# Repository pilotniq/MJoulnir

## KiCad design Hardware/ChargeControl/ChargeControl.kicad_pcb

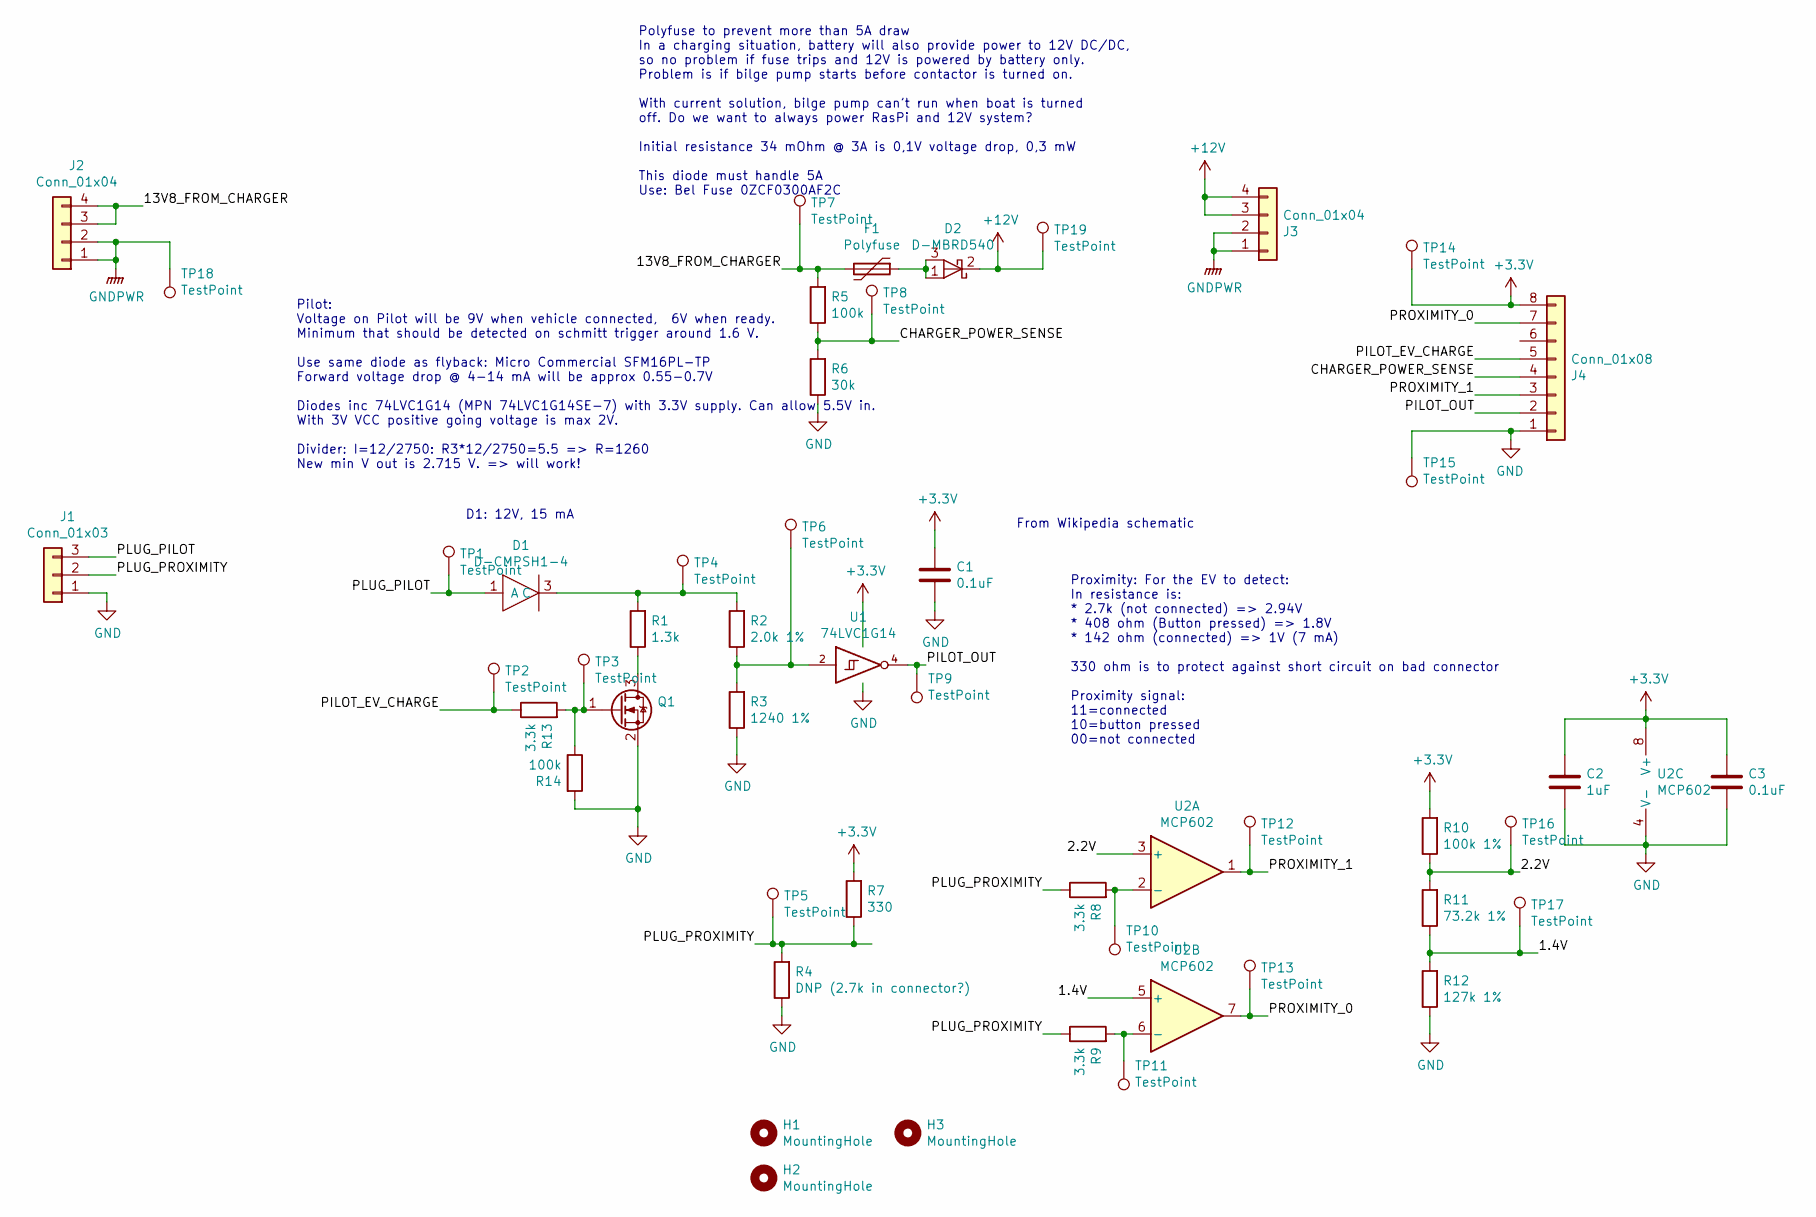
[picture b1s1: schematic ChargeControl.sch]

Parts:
C1, C3: 0.1uF; C_0603_1608Metric_Pad1.05x0.95mm_HandSolder
C2: 1uF; C_0603_1608Metric_Pad1.05x0.95mm_HandSolder
D1: D-CMPSH1-4; SOT23F
D2: D-MBRD540; TO-252-3_TabPin2
F1: Polyfuse; Fuse_2920_7451Metric_Pad2.10x5.45mm_HandSolder
H1, H2, H3: MountingHole; MountingHole_4.3mm_M4_ISO14580
J1: Conn_01x03; CON-MOLEX-CGRIDIII-1x3-RA-0901362203
J2, J3: Conn_01x04; CON-MOLEX-CGRIDIII-1x4-RA-0901362204
J4: Conn_01x08; CON-MOLEX-CGRIDIII-2x4-RA-0901303208
Q1: Q-FET-N-SSM3K36MFV; SOT-723
R1: 1.3k; R_0603_1608Metric_Pad1.05x0.95mm_HandSolder
R2: 2.0k 1%; R_0603_1608Metric_Pad1.05x0.95mm_HandSolder
R3: 1240 1%; R_0603_1608Metric_Pad1.05x0.95mm_HandSolder
R4: DNP (2.7k in connector?); R_0603_1608Metric_Pad1.05x0.95mm_HandSolder
R5, R14: 100k; R_0603_1608Metric_Pad1.05x0.95mm_HandSolder
R6: 30k; R_0603_1608Metric_Pad1.05x0.95mm_HandSolder
R7: 330; R_0603_1608Metric_Pad1.05x0.95mm_HandSolder
R8, R9, R13: 3.3k; R_0603_1608Metric_Pad1.05x0.95mm_HandSolder
R10: 100k 1%; R_0603_1608Metric_Pad1.05x0.95mm_HandSolder
R11: 73.2k 1%; R_0603_1608Metric_Pad1.05x0.95mm_HandSolder
R12: 127k 1%; R_0603_1608Metric_Pad1.05x0.95mm_HandSolder
TP1, TP2, TP3, TP4, TP5, TP6, TP7, TP8, TP9, TP10, TP11, TP12, TP13, TP14, TP15, TP16, TP17, TP18, TP19: TestPoint; TestPoint_Loop_D2.50mm_Drill1.0mm_LowProfile
U1: 74LVC1G14; SOT-353_SC-70-5_Handsoldering
U2: MCP602; SOIC-8_3.9x4.9mm_P1.27mm

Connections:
+3V3: C1.1, C2.1, C3.1, J4.8, R7.2, R10.2, TP14.1, U1.5 (VCC), U2.8 (V+)
+12V: D2.2 (K), J3.3, J3.4, TP19.1
/1.4V: R11.1, R12.2, TP17.1, U2.5 (+)
/2.2V: R10.1, R11.2, TP16.1, U2.3 (+)
/13V8_FROM_CHARGER: F1.2, J2.3, J2.4, R5.2, TP7.1
/CHARGER_POWER_SENSE: J4.4, R5.1, R6.2, TP8.1
/PILOT_EV_CHARGE: J4.5, R13.1, TP2.1
/PILOT_OUT: J4.2, TP9.1, U1.4
/PLUG_PILOT: D1.1 (A), J1.3, TP1.1
/PLUG_PROXIMITY: J1.2, R4.2, R7.1, R8.1, R9.1, TP5.1
/PROXIMITY_0: J4.7, TP13.1, U2.7
/PROXIMITY_1: J4.3, TP12.1, U2.1
GND: C1.2, C2.2, C3.2, J1.1, J4.1, Q1.2 (S), R3.1, R4.1, R6.1, R12.1, R14.2, TP15.1, U1.3 (GND), U2.4 (V-)
GNDPWR: J2.1, J2.2, J3.1, J3.2, TP18.1
unnamed: D1.3 (C), R1.2, R2.2, TP4.1
unnamed: D2.1 (A), D2.3, F1.1
unnamed: Q1.1 (G), R13.2, R14.1, TP3.1
unnamed: Q1.3 (D), R1.1
unnamed: R2.1, R3.2, TP6.1, U1.2
unnamed: R8.2, TP10.1, U2.2 (-)
unnamed: R9.2, TP11.1, U2.6 (-)

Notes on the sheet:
Polyfuse to prevent more than 5A draw In a charging situation, battery will also provide power to 12V DC/DC, so no problem if fuse trips and 12V is powered by battery only. Problem is if bilge pump starts before contactor is turned on. With current solution, bilge pump can’t run when boat is turned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
From Wikipedia schematic
D1: 12V, 15 mA
Proximity: For the EV to detect: In resistance is: * 2.7k (not connected) => 2.94V * 408 ohm (Button pressed) => 1.8V * 142 ohm (connected) => 1V (7 mA) 330 ohm is to protect against short circuit on bad connector Proximity signal: 11=connected 10=button pressed 00=not connected
Pilot: Voltage on Pilot will be 9V when vehicle connected, 6V when ready. Minimum that should be detected on schmitt trigger around 1.6 V. Use same diode as flyback: Micro Commercial SFM16PL-TP Forward voltage drop @ 4-14 mA will be approx 0.55-0.7V Diodes inc 74LVC1G14 (MPN 74LVC1G14SE-7) with 3.3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

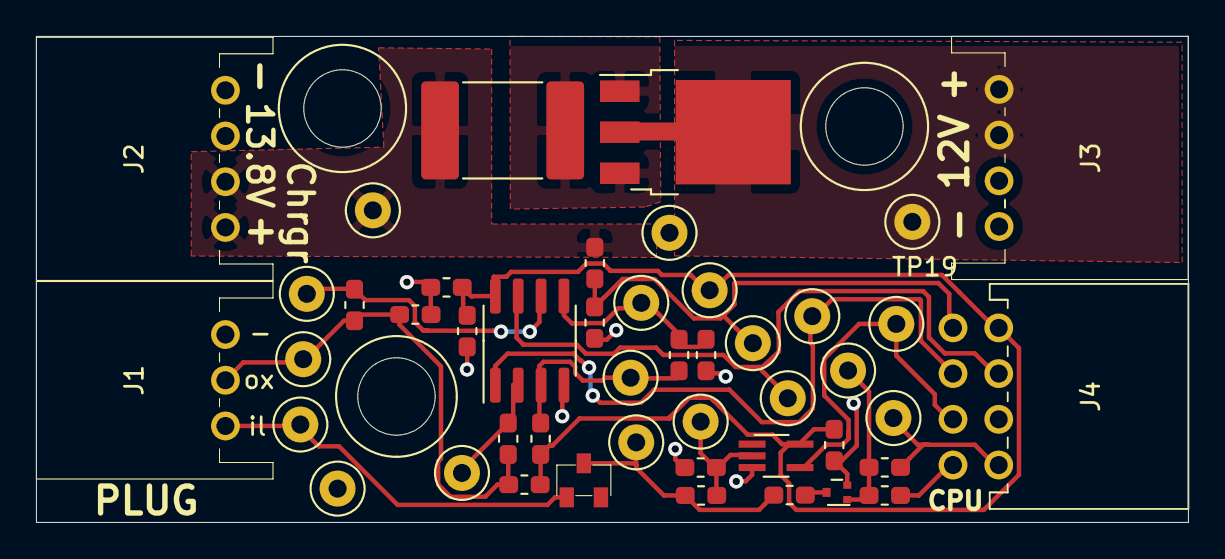
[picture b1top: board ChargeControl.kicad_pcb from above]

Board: 2 copper layers, 64.0 x 27.0 mm, 49 parts (0 on the bottom side), 21 nets.

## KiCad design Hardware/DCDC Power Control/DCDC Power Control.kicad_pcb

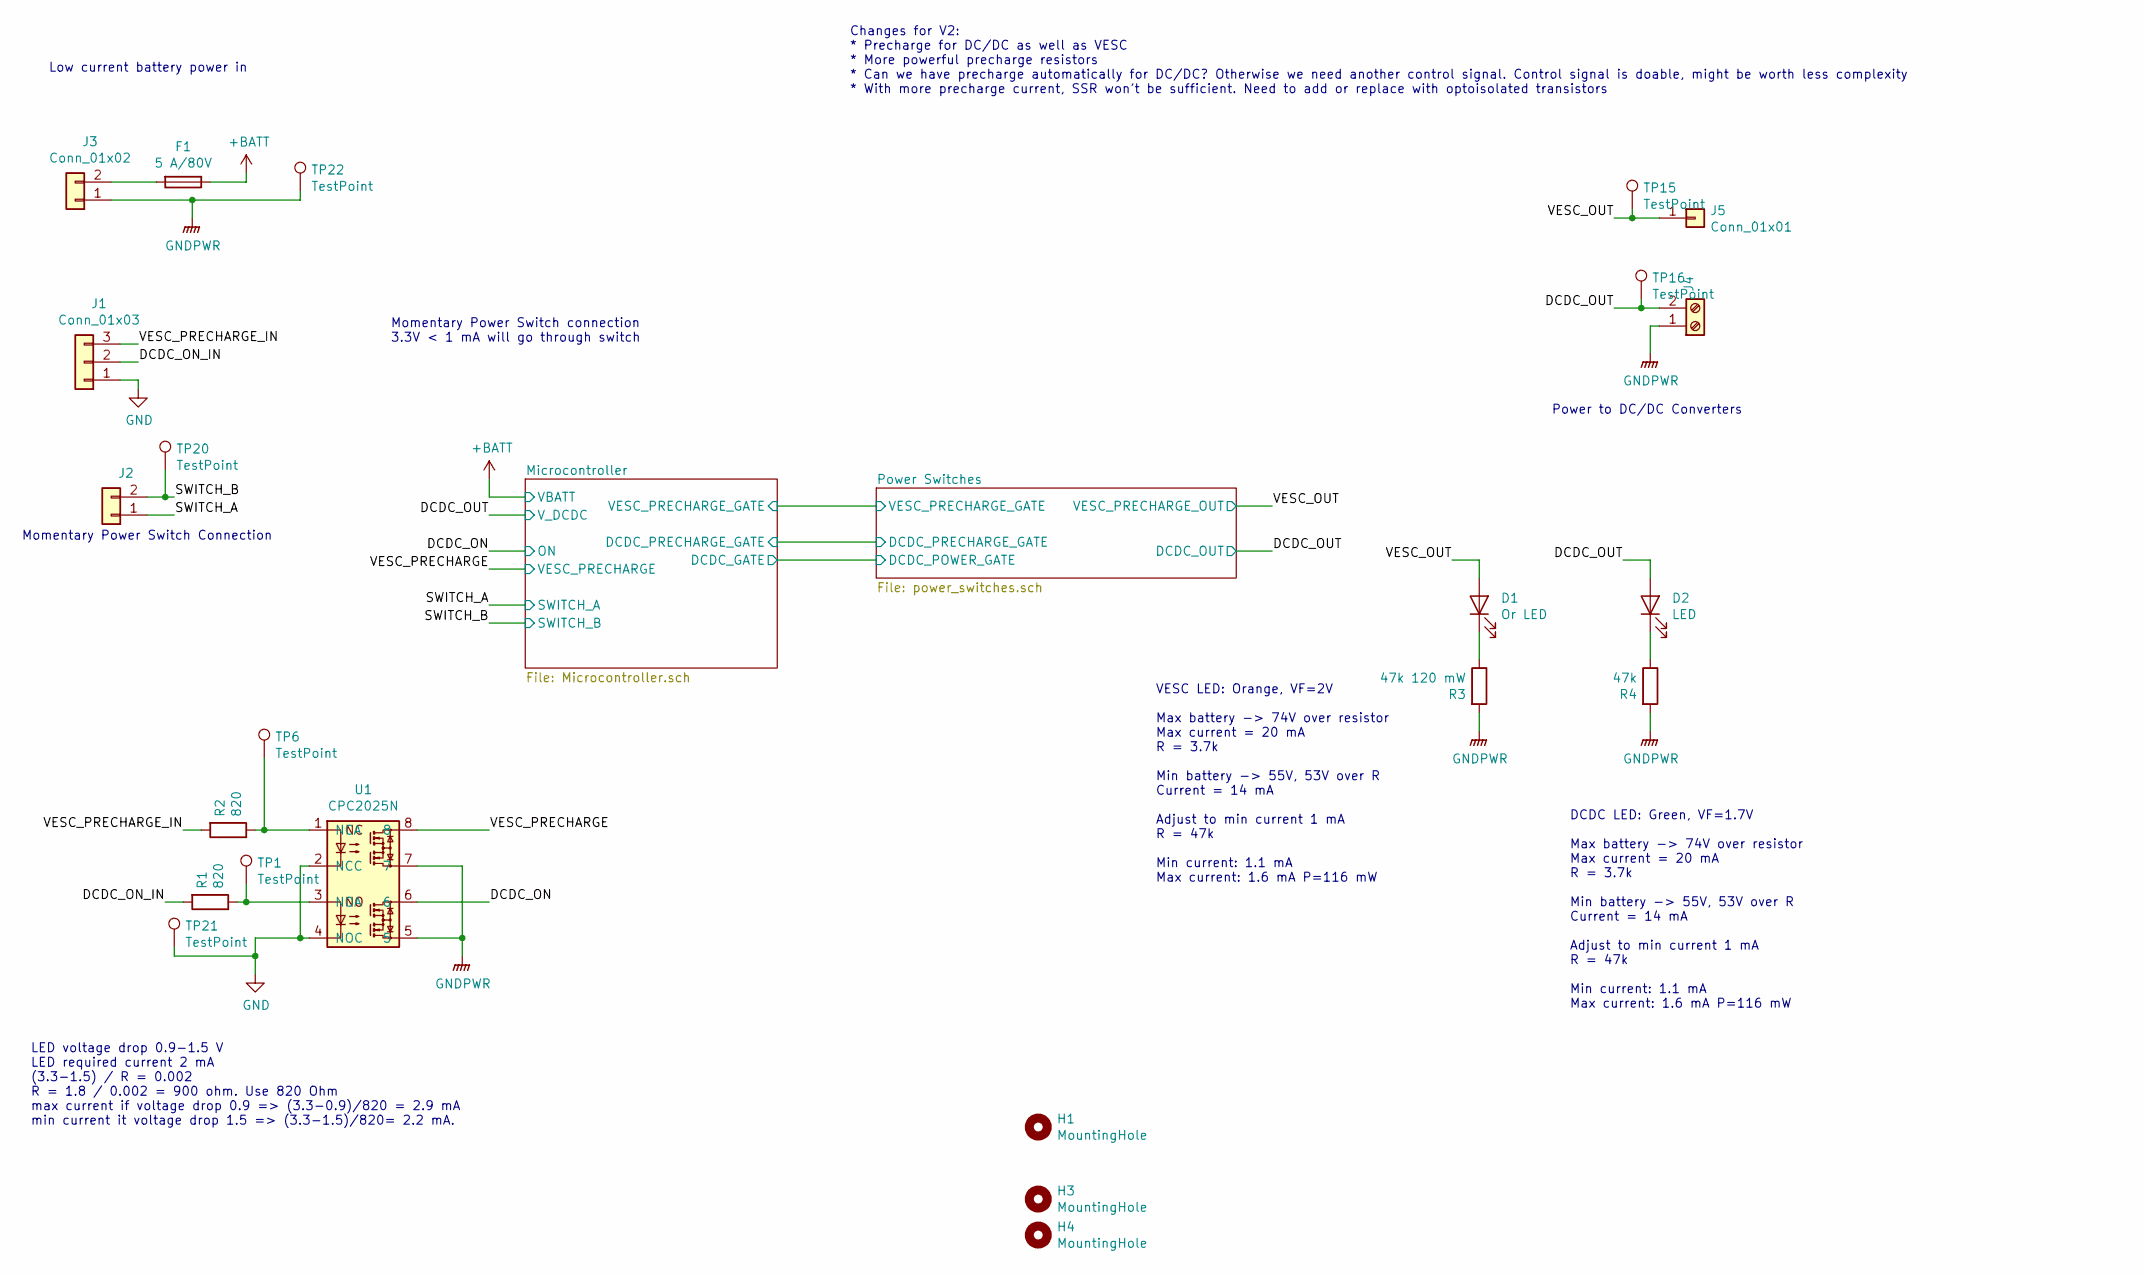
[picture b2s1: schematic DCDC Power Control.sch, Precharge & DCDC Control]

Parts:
D1: Or LED; LED_0603_1608Metric_Pad1.05x0.95mm_HandSolder
D2: LED; LED_0603_1608Metric_Pad1.05x0.95mm_HandSolder
F1: 5 A/80V; FUSE-KEYSTONE-3557-2
H1, H3, H4: MountingHole; MountingHole_4.3mm_M4_ISO14580
J1: Conn_01x03; CON-MOLEX-CGRIDIII-1x3-RA-0901362203
J2: Conn_01x02; CON-MOLEX-CGRIDIII-1x2 RA-0901362202
J3: Conn_01x02; AMASS_XT30PW-M_1x02_P2.50mm_Horizontal
J4: Screw_Terminal_01x02; AMASS_XT30PW-F_1x02_P2.50mm_Horizontal
J5: Conn_01x01; CON-SCREW-KEYSTONE-VERTICAL
R1, R2: 820; R_0603_1608Metric_Pad1.05x0.95mm_HandSolder
R3: 47k 120 mW; R_0603_1608Metric_Pad1.05x0.95mm_HandSolder
R4: 47k; R_0603_1608Metric_Pad1.05x0.95mm_HandSolder
TP1, TP6, TP15, TP16, TP20, TP21, TP22: TestPoint; TestPoint_Loop_D2.50mm_Drill1.0mm_LowProfile
U1: CPC2025N; SOIC-8_9.3x3.8mm_P2.54mm

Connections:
+BATT: F1.1; also elsewhere on the board
/DCDC_ON: U1.6; also elsewhere on the board
/DCDC_ON_IN: J1.2, R1.2
/DCDC_OUT: D2.2 (A), J4.2, TP16.1; also elsewhere on the board
/SWITCH_B: J2.2, TP20.1; also elsewhere on the board
/VESC_OUT: D1.2 (A), J5.1, TP15.1; also elsewhere on the board
/VESC_PRECHARGE: U1.8; also elsewhere on the board
/VESC_PRECHARGE_IN: J1.3, R2.2
GND: J1.1, TP21.1, U1.2 (NCC), U1.4 (NOC)
GNDPWR: J2.1, J3.1, J4.1, R3.2, R4.2, TP22.1, U1.5, U1.7; also elsewhere on the board
unnamed: D1.1 (K), R3.1
unnamed: D2.1 (K), R4.1
unnamed: F1.2, J3.2
unnamed: R1.1, TP1.1, U1.3 (NOA)
unnamed: R2.1, TP6.1, U1.1 (NCA)

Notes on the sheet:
Low current battery power in
Momentary Power Switch Connection
Power to DC/DC Converters
Momentary Power Switch connection 3.3V < 1 mA will go through switch
LED voltage drop 0.9-1.5 V LED required current 2 mA (3.3-1.5) / R = 0.002 R = 1.8 / 0.002 = 900 ohm. Use 820 Ohm max current if voltage drop 0.9 => (3.3-0.9)/820 = 2.9 mA min current it voltage drop 1.5 => (3.3-1.5)/820= 2.2 mA.
Changes for V2: * Precharge for DC/DC as well as VESC * More powerful precharge resistors * Can we have precharge automatically for DC/DC? Otherwise we need another control signal. Control signal is doable, might be worth less complexity * With more precharge current, SSR won’t be sufficient. Need 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
VESC LED: Orange, VF=2V Max battery -> 74V over resistor Max current = 20 mA R = 3.7k Min battery -> 55V, 53V over R Current = 14 mA Adjust to min current 1 mA R = 47k Min current: 1.1 mA Max current: 1.6 mA P=116 mW
DCDC LED: Green, VF=1.7V Max battery -> 74V over resistor Max current = 20 mA R = 3.7k Min battery -> 55V, 53V over R Current = 14 mA Adjust to min current 1 mA R = 47k Min current: 1.1 mA Max current: 1.6 mA P=116 mW

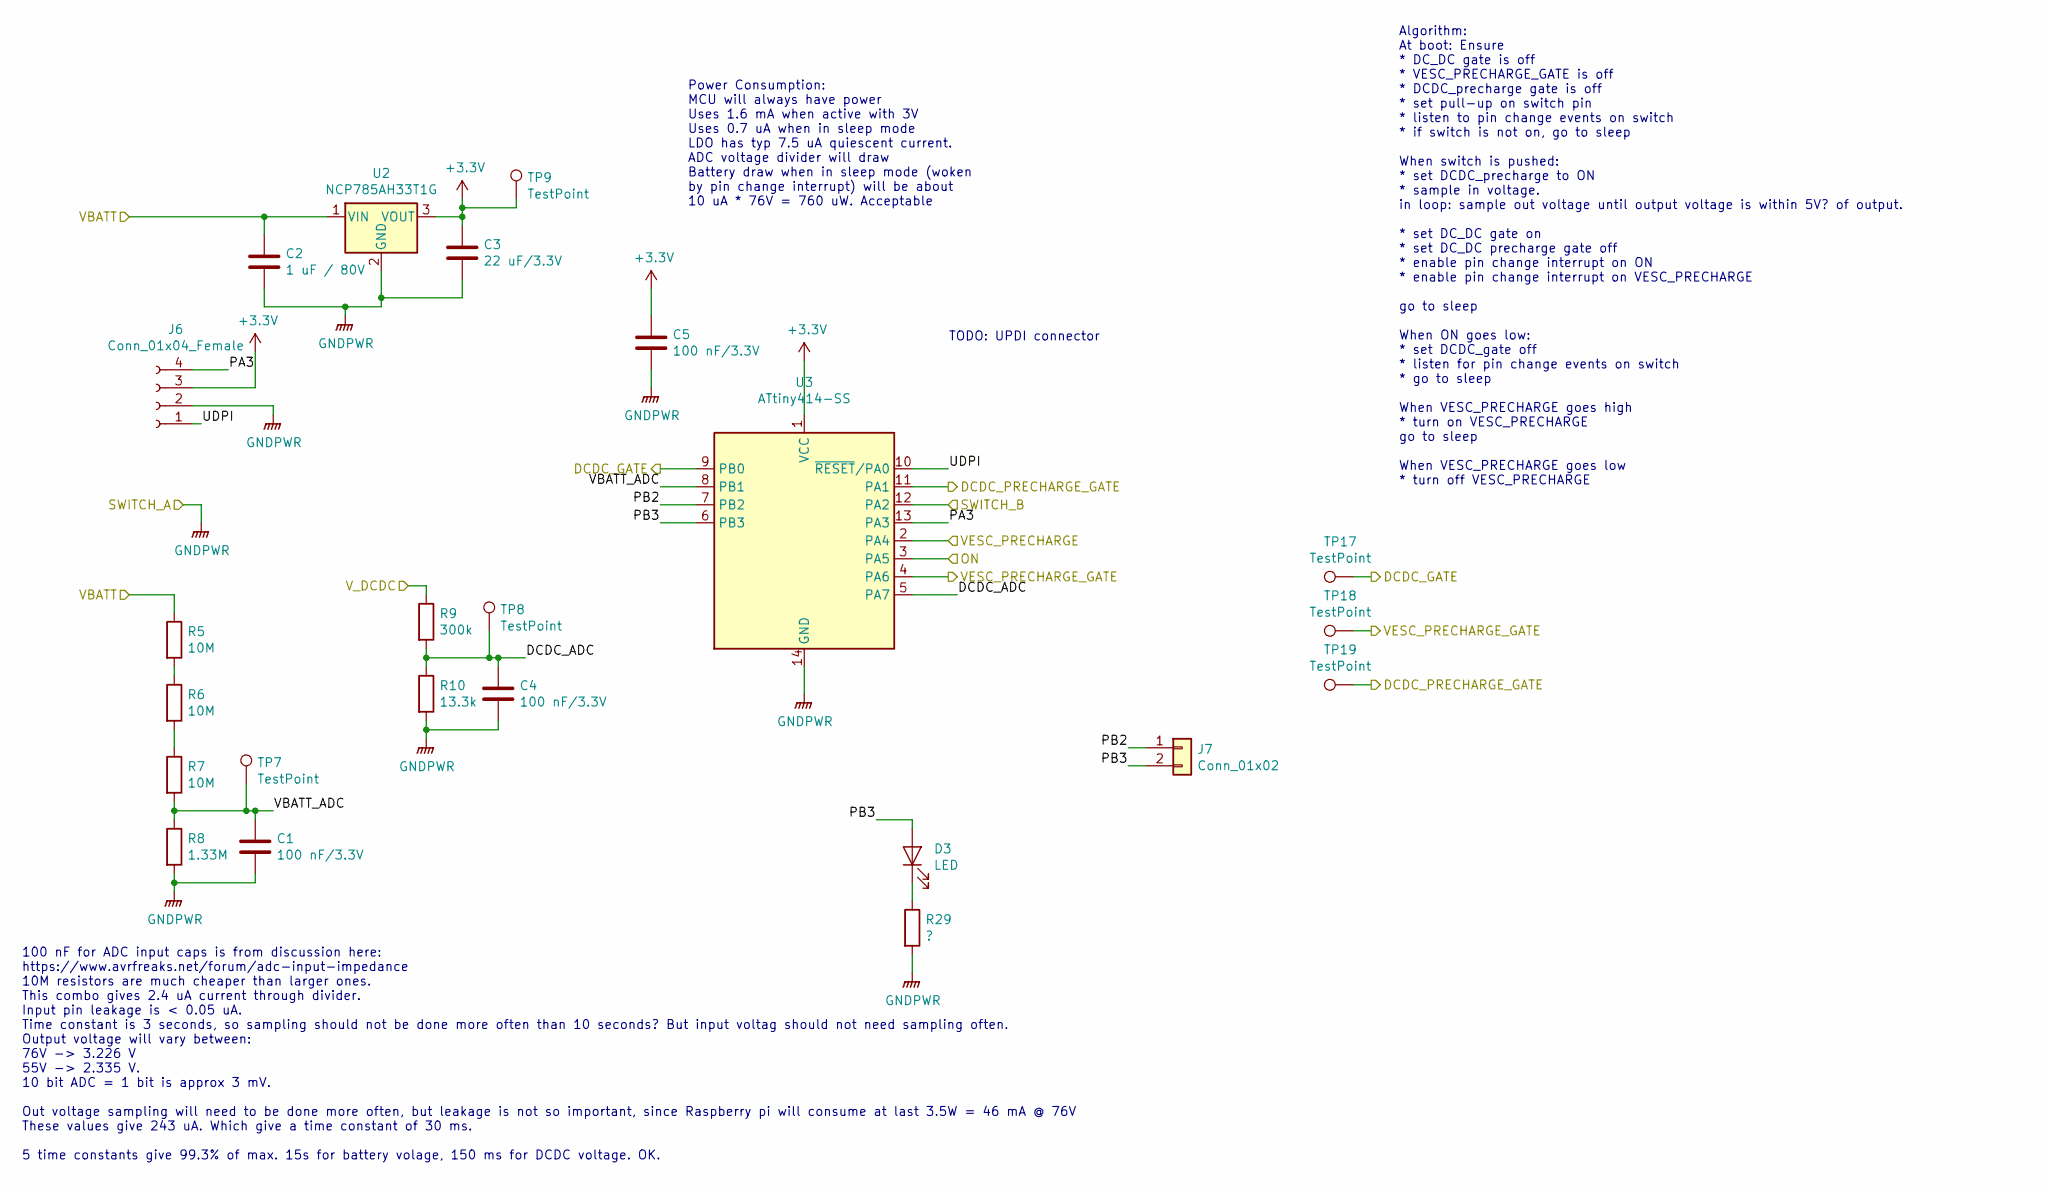
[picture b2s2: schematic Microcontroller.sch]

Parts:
C1, C4, C5: 100 nF/3.3V; C_0603_1608Metric_Pad1.05x0.95mm_HandSolder
C2: 1 uF / 80V; C_1206_3216Metric_Pad1.42x1.75mm_HandSolder
C3: 22 uF/3.3V; C_0805_2012Metric_Pad1.15x1.40mm_HandSolder
D3: LED; LED_0603_1608Metric_Castellated
J6: Conn_01x04_Female; PinSocket_1x04_P2.54mm_Vertical
J7: Conn_01x02; PinHeader_1x02_P2.54mm_Vertical
R5, R6, R7: 10M; R_0603_1608Metric_Pad1.05x0.95mm_HandSolder
R8: 1.33M; R_0603_1608Metric_Pad1.05x0.95mm_HandSolder
R9: 300k; R_0603_1608Metric_Pad1.05x0.95mm_HandSolder
R10: 13.3k; R_0603_1608Metric_Pad1.05x0.95mm_HandSolder
R29: ?; R_0603_1608Metric_Pad1.05x0.95mm_HandSolder
TP7, TP8, TP9, TP17, TP18, TP19: TestPoint; TestPoint_Loop_D2.50mm_Drill1.0mm_LowProfile
U2: NCP785AH33T1G; SOT-89-3
U3: ATtiny414-SS; SOIC-14_3.9x8.7mm_P1.27mm

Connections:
+3V3: C3.1, C5.1, J6.3, TP9.1, U2.3 (VOUT), U3.1 (VCC)
+BATT: C2.1, R5.1, U2.1 (VIN); also elsewhere on the board
/DCDC_ON: U3.3 (PA5); also elsewhere on the board
/DCDC_OUT: R9.1; also elsewhere on the board
/Microcontroller/DCDC_ADC: C4.1, R9.2, R10.1, TP8.1, U3.5 (PA7)
/Microcontroller/DCDC_GATE: TP17.1, U3.9 (PB0); also elsewhere on the board
/Microcontroller/DCDC_PRECHARGE_GATE: TP19.1, U3.11 (PA1); also elsewhere on the board
/Microcontroller/PA3: J6.4, U3.13 (PA3)
/Microcontroller/PB2: J7.1, U3.7 (PB2)
/Microcontroller/PB3: D3.2 (A), J7.2, U3.6 (PB3)
/Microcontroller/UDPI: J6.1, U3.10 (~RESET~/PA0)
/Microcontroller/VBATT_ADC: C1.1, R7.2, R8.1, TP7.1, U3.8 (PB1)
/Microcontroller/VESC_PRECHARGE_GATE: TP18.1, U3.4 (PA6); also elsewhere on the board
/SWITCH_B: U3.12 (PA2); also elsewhere on the board
/VESC_PRECHARGE: U3.2 (PA4); also elsewhere on the board
GNDPWR: C1.2, C2.2, C3.2, C4.2, C5.2, J6.2, R8.2, R10.2, R29.2, U2.2 (GND), U3.14 (GND); also elsewhere on the board
unnamed: D3.1 (K), R29.1
unnamed: R5.2, R6.1
unnamed: R6.2, R7.1

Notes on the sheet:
Power Consumption: MCU will always have power Uses 1.6 mA when active with 3V Uses 0.7 uA when in sleep mode LDO has typ 7.5 uA quiescent current. ADC voltage divider will draw Battery draw when in sleep mode (woken by pin change interrupt) will be about 10 uA * 76V = 760 uW. Acceptable
100 nF for ADC input caps is from discussion here: https://www.avrfreaks.net/forum/adc-input-impedance 10M resistors are much cheaper than larger ones. This combo gives 2.4 uA current through divider. Input pin leakage is < 0.05 uA. Time constant is 3 seconds, so sampling should not be done more of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
Algorithm: At boot: Ensure * DC_DC gate is off * VESC_PRECHARGE_GATE is off * DCDC_precharge gate is off * set pull-up on switch pin * listen to pin change events on switch * if switch is not on, go to sleep When switch is pushed: * set DCDC_precharge to ON * sample in voltage. in loop: sample out 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
TODO: UPDI connector

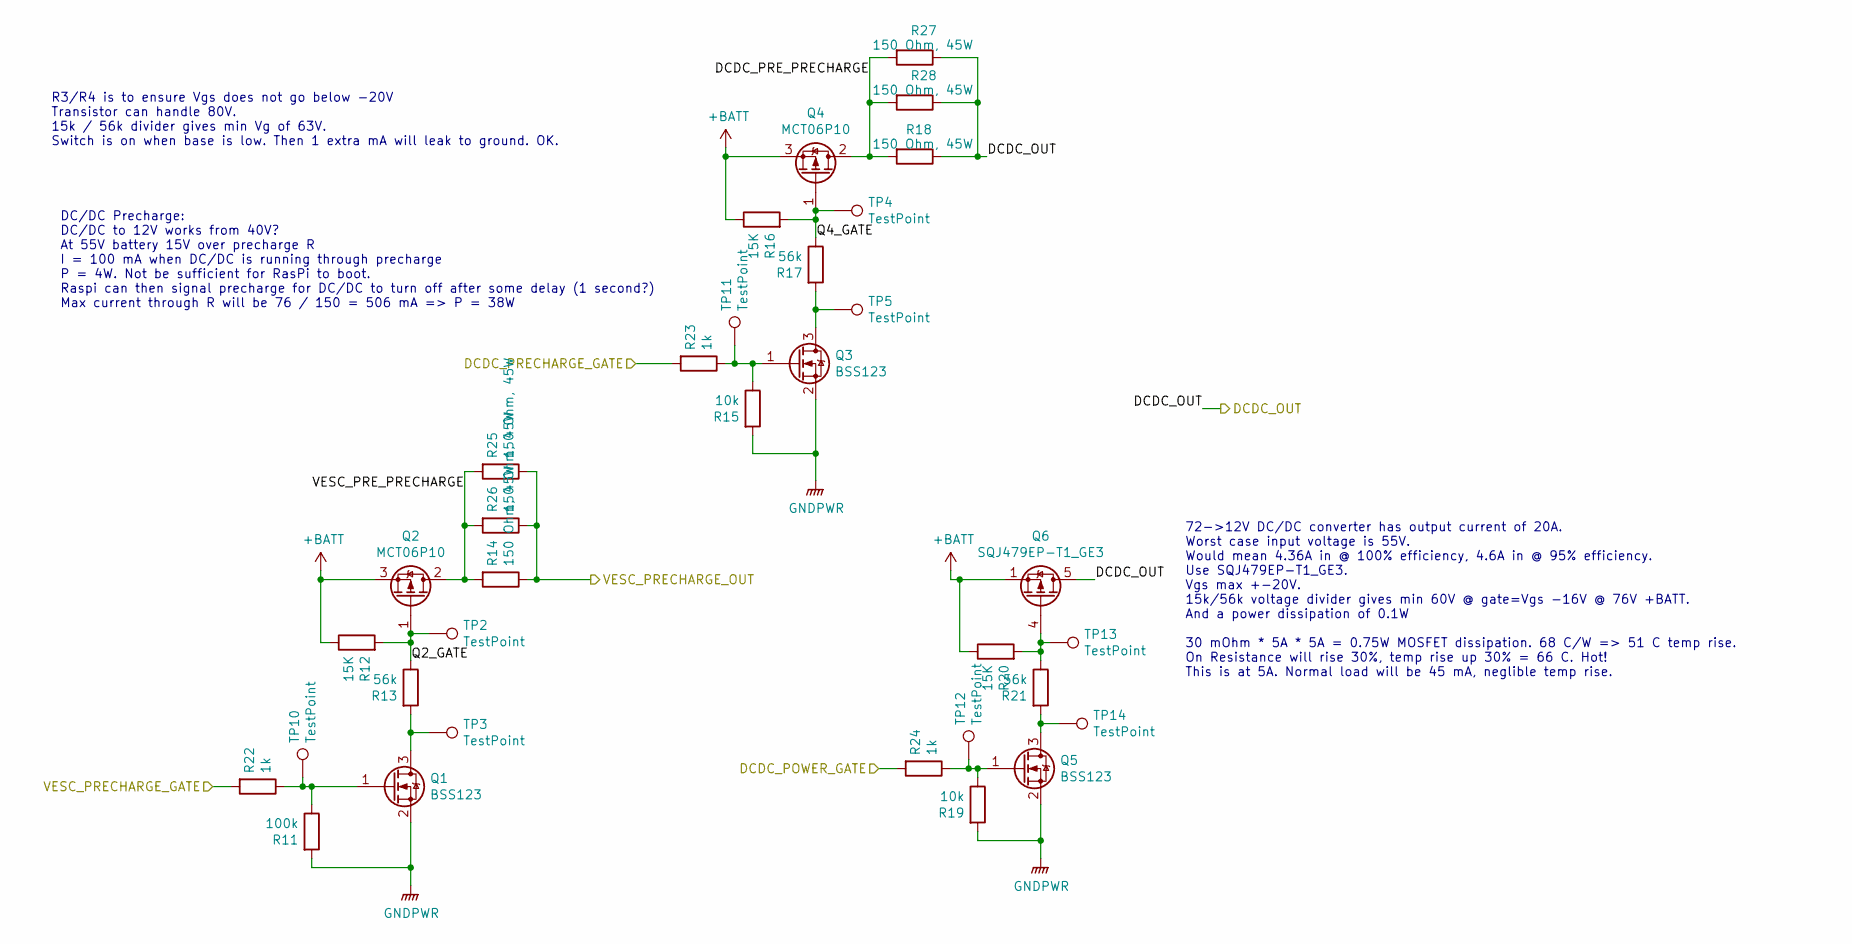
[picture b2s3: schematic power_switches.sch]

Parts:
Q1, Q3, Q5: BSS123; SOT-23
Q2, Q4: MCT06P10; SOT-223-3_TabPin2
Q6: SQJ479EP-T1_GE3; Q-VISHAY-PowerPAK SO-8L Single
R11: 100k; R_0603_1608Metric_Pad1.05x0.95mm_HandSolder
R12, R16, R20: 15K; R_0603_1608Metric_Pad1.05x0.95mm_HandSolder
R13, R17, R21: 56k; R_0603_1608Metric_Pad1.05x0.95mm_HandSolder
R14, R18, R25, R26, R27, R28: 150 Ohm, 45W; R_Radial_Power_L13.0mm_W9.0mm_P5.00mm
R15, R19: 10k; R_0603_1608Metric_Pad1.05x0.95mm_HandSolder
R22, R23, R24: 1k; R_0603_1608Metric_Pad1.05x0.95mm_HandSolder
TP2, TP3, TP4, TP5, TP10, TP11, TP12, TP13, TP14: TestPoint; TestPoint_Loop_D2.50mm_Drill1.0mm_LowProfile

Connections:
+BATT: Q2.3 (S), Q4.3 (S), Q6.1 (S), Q6.2 (S), Q6.3 (S), R12.1, R16.1, R20.1; also elsewhere on the board
/DCDC_OUT: Q6.5 (D), R18.1, R27.1, R28.1; also elsewhere on the board
/Microcontroller/DCDC_GATE: R24.2; also elsewhere on the board
/Microcontroller/DCDC_PRECHARGE_GATE: R23.2; also elsewhere on the board
/Microcontroller/VESC_PRECHARGE_GATE: R22.2; also elsewhere on the board
/Power Switches/DCDC_PRE_PRECHARGE: Q4.2 (D), R18.2, R27.2, R28.2
/Power Switches/Q2_GATE: Q2.1 (G), R12.2, R13.1, TP2.1
/Power Switches/Q4_GATE: Q4.1 (G), R16.2, R17.1, TP4.1
/Power Switches/VESC_PRE_PRECHARGE: Q2.2 (D), R14.2, R25.2, R26.2
/VESC_OUT: R14.1, R25.1, R26.1; also elsewhere on the board
GNDPWR: Q1.2 (S), Q3.2 (S), Q5.2 (S), R11.2, R15.2, R19.2; also elsewhere on the board
unnamed: Q1.1 (G), R11.1, R22.1, TP10.1
unnamed: Q1.3 (D), R13.2, TP3.1
unnamed: Q3.1 (G), R15.1, R23.1, TP11.1
unnamed: Q3.3 (D), R17.2, TP5.1
unnamed: Q5.1 (G), R19.1, R24.1, TP12.1
unnamed: Q5.3 (D), R21.2, TP14.1
unnamed: Q6.4 (G), R20.2, R21.1, TP13.1

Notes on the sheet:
R3/R4 is to ensure Vgs does not go below -20V Transistor can handle 80V. 15k / 56k divider gives min Vg of 63V. Switch is on when base is low. Then 1 extra mA will leak to ground. OK.
72->12V DC/DC converter has output current of 20A. Worst case input voltage is 55V. Would mean 4.36A in @ 100% efficiency, 4.6A in @ 95% efficiency. Use SQJ479EP-T1_GE3. Vgs max +-20V. 15k/56k voltage divider gives min 60V @ gate=Vgs -16V @ 76V +BATT. And a power dissipation of 0.1W 30 mOhm * 5A * 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
DC/DC Precharge: DC/DC to 12V works from 40V? At 55V battery 15V over precharge R I = 100 mA when DC/DC is running through precharge P = 4W. Not be sufficient for RasPi to boot. Raspi can then signal precharge for DC/DC to turn off after some delay (1 second?) Max current through R will be 76 / 150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

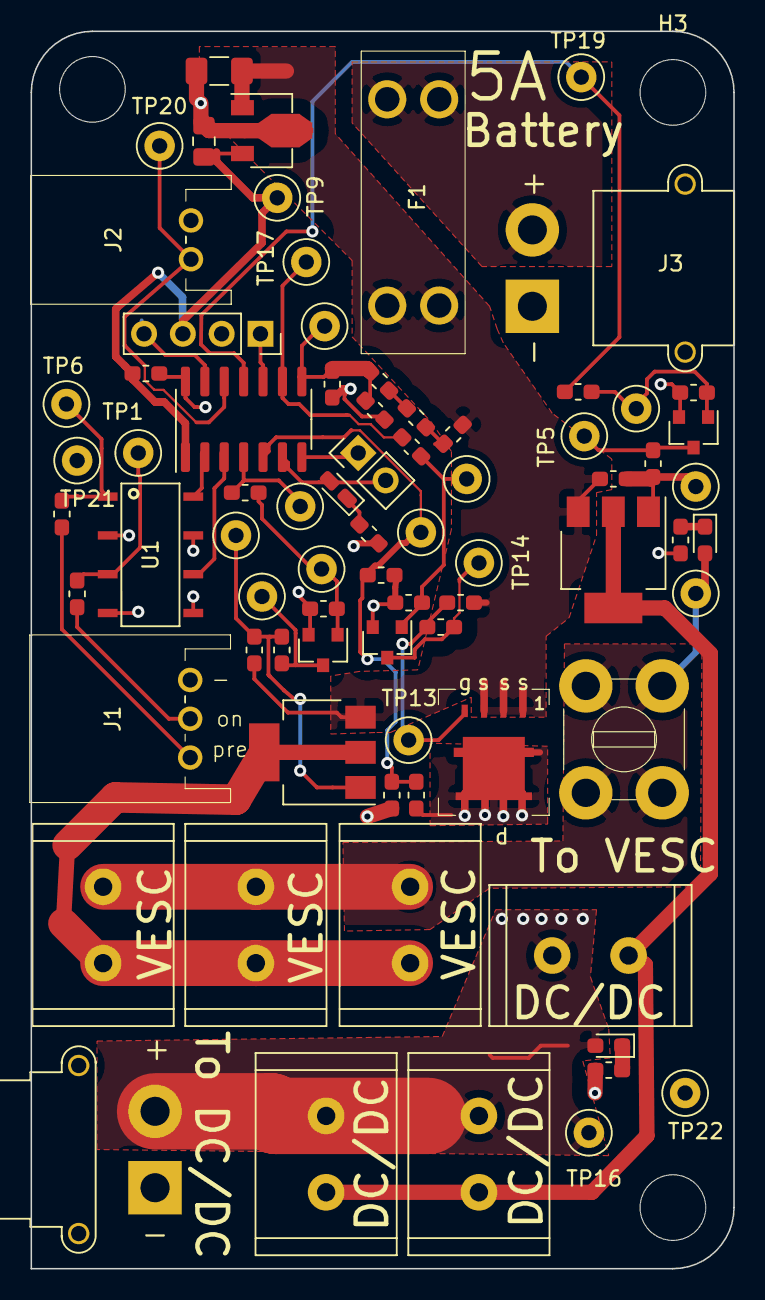
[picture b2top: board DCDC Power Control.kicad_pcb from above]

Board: 2 copper layers, 46.0 x 81.0 mm, 79 parts (0 on the bottom side), 39 nets.

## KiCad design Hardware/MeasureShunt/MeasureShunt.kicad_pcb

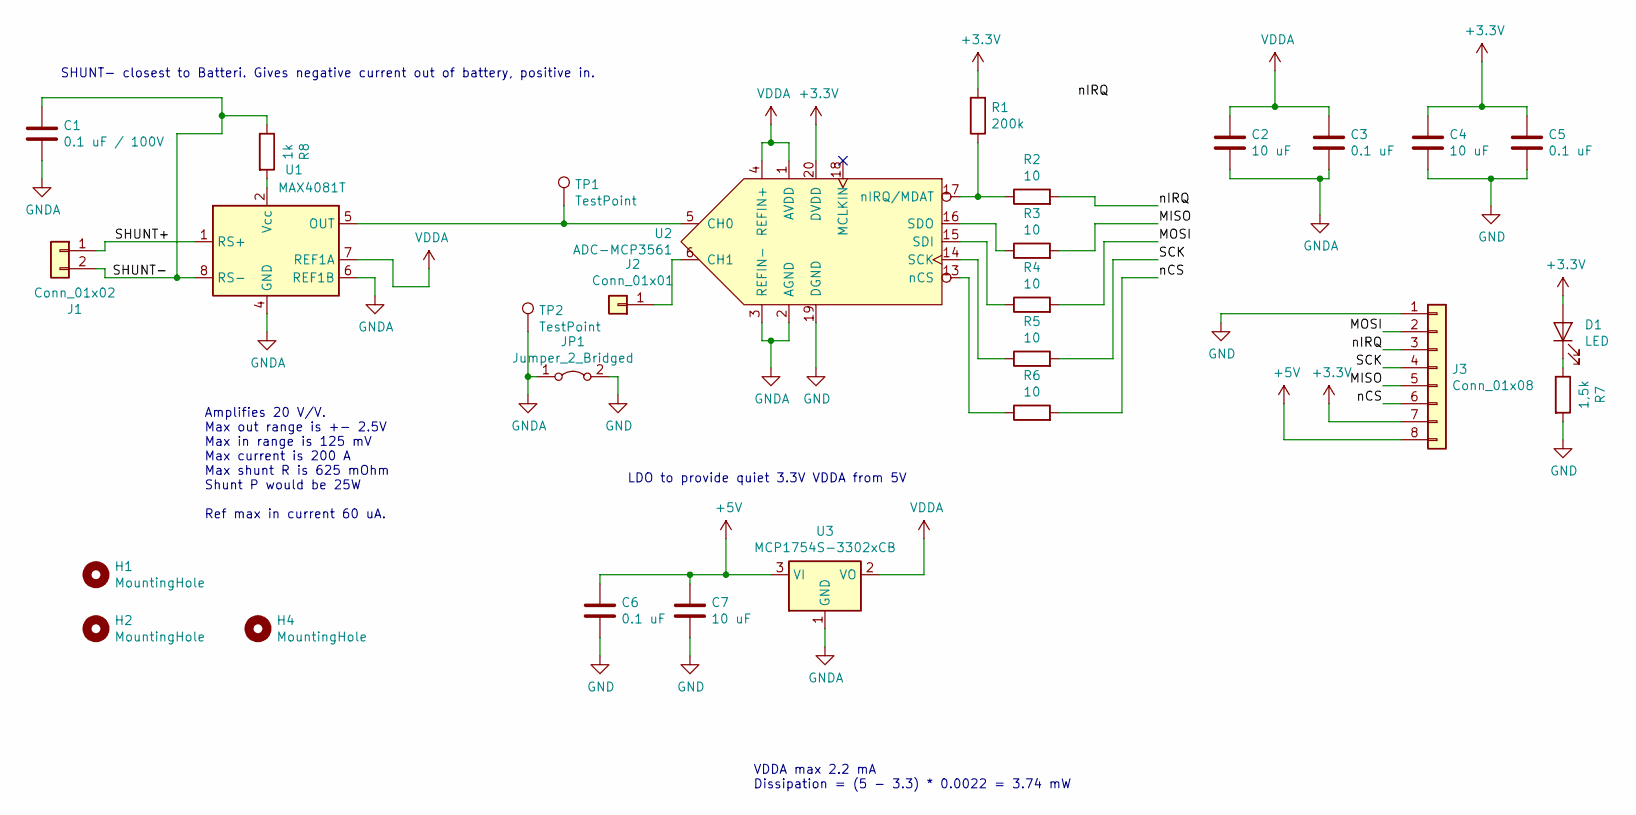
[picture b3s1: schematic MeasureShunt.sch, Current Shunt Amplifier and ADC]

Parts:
C1: 0.1 uF / 100V; C_0805_2012Metric_Pad1.15x1.40mm_HandSolder
C2, C4, C7: 10 uF; C_0603_1608Metric_Pad1.05x0.95mm_HandSolder
C3, C5, C6: 0.1 uF; C_0603_1608Metric_Pad1.05x0.95mm_HandSolder
D1: LED; LED_0603_1608Metric_Pad1.05x0.95mm_HandSolder
H1, H2, H4: MountingHole; MountingHole_4.3mm_M4_ISO14580
J1: Conn_01x02; CON-MOLEX-CGRIDIII-1x2 RA-0901362202
J2: Conn_01x01; PinHeader_1x01_P2.54mm_Vertical
J3: Conn_01x08; CON-MOLEX-CGRIDIII-2x4-RA-0901303208
JP1: Jumper_2_Bridged; SolderJumper-2_P1.3mm_Bridged2Bar_Pad1.0x1.5mm
R1: 200k; R_0603_1608Metric_Pad1.05x0.95mm_HandSolder
R2, R3, R4, R5, R6: 10; R_0603_1608Metric_Pad1.05x0.95mm_HandSolder
R7: 1,5k; R_0603_1608Metric_Pad1.05x0.95mm_HandSolder
R8: 1k; R_0603_1608Metric_Pad1.05x0.95mm_HandSolder
TP1, TP2: TestPoint; TestPoint_Pad_D2.0mm
U1: MAX4081T; SOIC-8_3.9x4.9mm_P1.27mm
U2: ADC-MCP3561; TSSOP-20_4.4x6.5mm_P0.65mm
U3: MCP1754S-3302xCB; SOT-23

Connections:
+3V3: C4.1, C5.1, D1.2 (A), J3.7, R1.2, U2.20 (DVDD)
+5V: C6.1, C7.1, J3.8, U3.3 (VI)
/MISO: J3.5, R3.2
/MOSI: J3.2, R4.2
/SCK: J3.4, R5.2
/SHUNT+: J1.1, U1.1 (RS+)
/SHUNT-: C1.1, J1.2, R8.1, U1.8 (RS-)
/nCS: J3.6, R6.2
/nIRQ: J3.3, R2.2
GND: C4.2, C5.2, C6.2, C7.2, J3.1, JP1.2 (B), R7.2, U2.19 (DGND)
GNDA: C1.2, C2.2, C3.2, JP1.1 (A), TP2.1, U1.4 (GND), U1.6 (REF1B), U2.2 (AGND), U2.3 (REFIN-), U3.1 (GND)
unnamed: D1.1 (K), R7.1
unnamed: J2.1, U2.6 (CH1)
unnamed: R1.1, R2.1, U2.17 (nIRQ/MDAT)
unnamed: R3.1, U2.16 (SDO)
unnamed: R4.1, U2.15 (SDI)
unnamed: R5.1, U2.14 (SCK)
unnamed: R6.1, U2.13 (nCS)
unnamed: R8.2, U1.2 (Vcc)
unnamed: TP1.1, U1.5 (OUT), U2.5 (CH0)
VDDA: C2.1, C3.1, U1.7 (REF1A), U2.1 (AVDD), U2.4 (REFIN+), U3.2 (VO)

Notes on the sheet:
Amplifies 20 V/V. Max out range is +- 2.5V Max in range is 125 mV Max current is 200 A Max shunt R is 625 mOhm Shunt P would be 25W Ref max in current 60 uA.
SHUNT- closest to Batteri. Gives negative current out of battery, positive in.
VDDA max 2.2 mA Dissipation = (5 - 3.3) * 0.0022 = 3.74 mW
LDO to provide quiet 3.3V VDDA from 5V

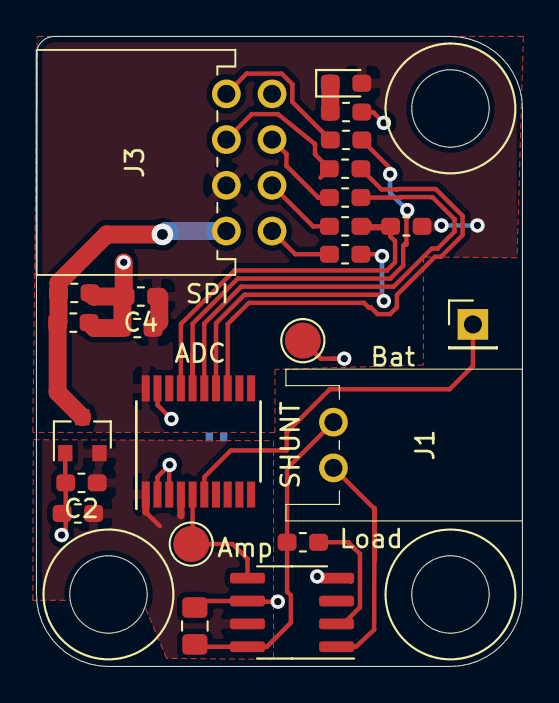
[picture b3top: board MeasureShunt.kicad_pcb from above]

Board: 2 copper layers, 27.0 x 35.0 mm, 28 parts (1 on the bottom side), 21 nets.
